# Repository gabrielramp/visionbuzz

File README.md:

# visionbuzz
A UCF Senior Design 1 project for a facial recognition vision assistant for vision-impaired users.

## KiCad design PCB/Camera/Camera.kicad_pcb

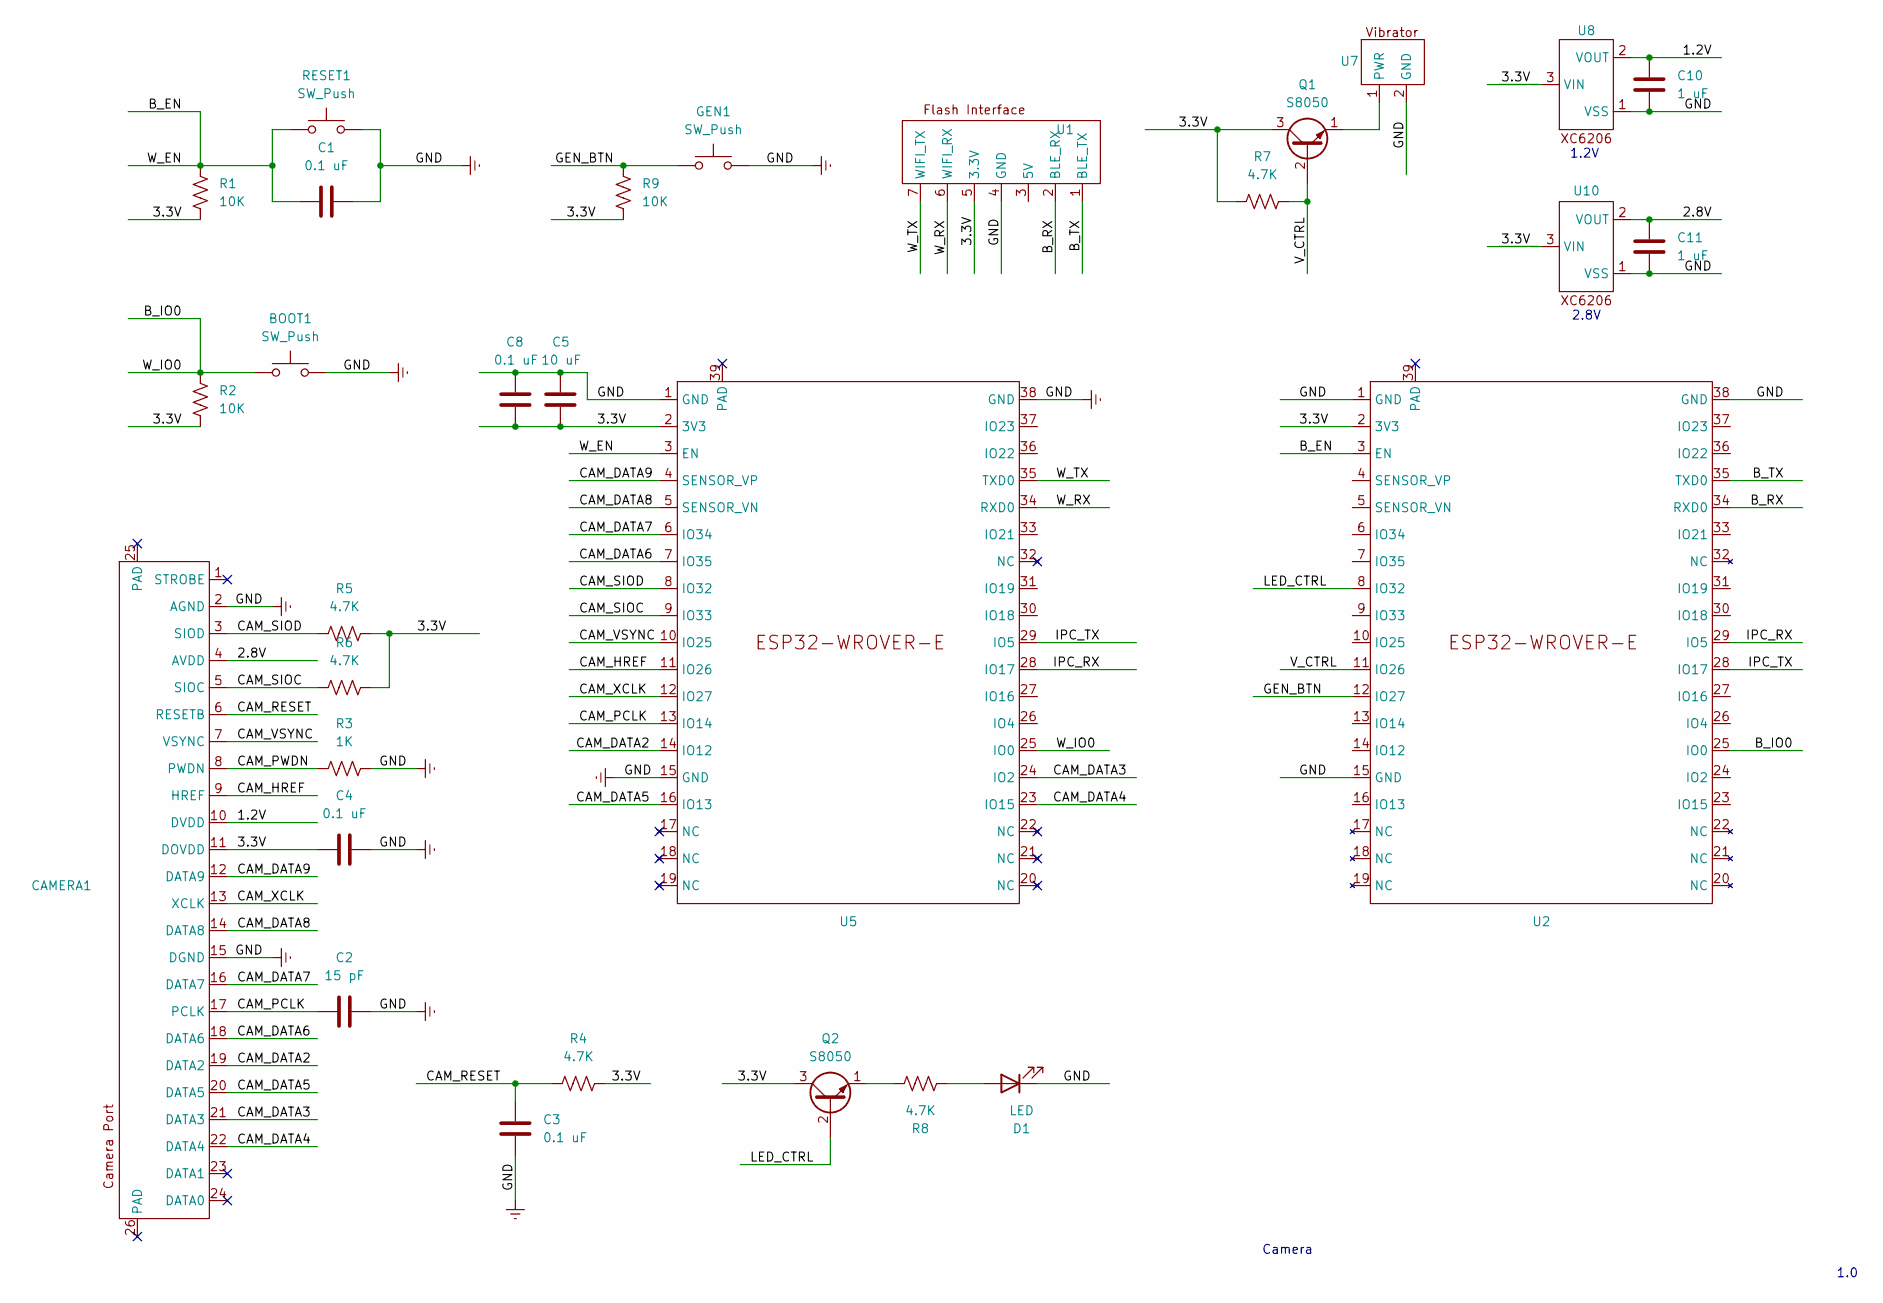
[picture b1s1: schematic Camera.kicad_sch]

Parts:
BOOT1: SW_Push; 6x6x4.3 SMD button
C1, C3, C4, C8: 0.1 uF; C_1206_3216Metric_Pad1.33x1.80mm_HandSolder
C2: 15 pF; C_1206_3216Metric_Pad1.33x1.80mm_HandSolder
C5: 10 uF; C_1206_3216Metric_Pad1.33x1.80mm_HandSolder
C10, C11: 1 uF; C_1206_3216Metric_Pad1.33x1.80mm_HandSolder
CAMERA1: 24-pin-FPC-0.5mm
D1: LED; vibration motor
GEN1: SW_Push; 6x6x4.3 SMD button
Q1, Q2: S8050; transistor
R1, R2, R9: 10K; R_1206_3216Metric_Pad1.30x1.75mm_HandSolder
R3: 1K; R_1206_3216Metric_Pad1.30x1.75mm_HandSolder
R4, R5, R6, R7, R8: 4.7K; R_1206_3216Metric_Pad1.30x1.75mm_HandSolder
RESET1: SW_Push; 6x6x4.3 SMD button
U1: Flash_Interface
U2, U5: ESP32-WROVER-E
U7: vibration motor
U8, U10: XC6206

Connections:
/1.2V: C10.2, CAMERA1.10 (DVDD), U8.2 (VOUT)
/2.8V: C11.2, CAMERA1.4 (AVDD), U10.2 (VOUT)
/3.3V: C4.1, C5.1, C8.2, CAMERA1.11 (DOVDD), Q1.3 (C), Q2.3 (C), R1.2, R2.2, R4.2, R5.1, R6.1, R7.2, R9.2, U1.5 (3.3V), U2.2 (3V3), U5.2 (3V3), U8.3 (VIN), U10.3 (VIN)
/B_EN: C1.1, R1.1, RESET1.1, U2.3 (EN), U5.3 (EN)
/B_IO0: BOOT1.1, R2.1, U2.25 (IO0), U5.25 (IO0)
/B_RX: U1.2 (BLE_RX), U2.34 (RXD0)
/B_TX: U1.1 (BLE_TX), U2.35 (TXD0)
/CAM_DATA2: CAMERA1.19 (DATA2), U5.14 (IO12)
/CAM_DATA3: CAMERA1.21 (DATA3), U5.24 (IO2)
/CAM_DATA4: CAMERA1.22 (DATA4), U5.23 (IO15)
/CAM_DATA5: CAMERA1.20 (DATA5), U5.16 (IO13)
/CAM_DATA6: CAMERA1.18 (DATA6), U5.7 (IO35)
/CAM_DATA7: CAMERA1.16 (DATA7), U5.6 (IO34)
/CAM_DATA8: CAMERA1.14 (DATA8), U5.5 (SENSOR_VN)
/CAM_DATA9: CAMERA1.12 (DATA9), U5.4 (SENSOR_VP)
/CAM_HREF: CAMERA1.9 (HREF), U5.11 (IO26)
/CAM_PCLK: C2.1, CAMERA1.17 (PCLK), U5.13 (IO14)
/CAM_PWDN: CAMERA1.8 (PWDN), R3.1
/CAM_RESET: C3.2, CAMERA1.6 (RESETB), R4.1
/CAM_SIOC: CAMERA1.5 (SIOC), R6.2, U5.9 (IO33)
/CAM_SIOD: CAMERA1.3 (SIOD), R5.2, U5.8 (IO32)
/CAM_VSYNC: CAMERA1.7 (VSYNC), U5.10 (IO25)
/CAM_XCLK: CAMERA1.13 (XCLK), U5.12 (IO27)
/GEN_BTN: GEN1.1, R9.1, U2.12 (IO27)
/IPC_RX: U2.29 (IO5), U5.28 (IO17)
/IPC_TX: U2.28 (IO17), U5.29 (IO5)
/LED_CTRL: Q2.2 (B), U2.8 (IO32)
/V_CTRL: Q1.2 (B), R7.1, U2.11 (IO26)
/W_RX: U1.6 (WIFI_RX), U5.34 (RXD0)
/W_TX: U1.7 (WIFI_TX), U5.35 (TXD0)
GNDREF: BOOT1.2, C1.2, C2.2, C3.1, C4.2, C5.2, C8.1, C10.1, C11.1, CAMERA1.2 (AGND), CAMERA1.15 (DGND), D1.1 (K), GEN1.2, R3.2, RESET1.2, U1.4 (GND), U2.1 (GND), U2.15 (GND), U2.38 (GND), U5.1 (GND), U5.15 (GND), U5.38 (GND), U7.2 (GND), U8.1 (VSS), U10.1 (VSS)
unnamed: D1.2 (A), R8.1
unnamed: Q1.1 (E), U7.1 (PWR)
unnamed: Q2.1 (E), R8.2

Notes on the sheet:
Camera
1.2V
2.8V
1.0

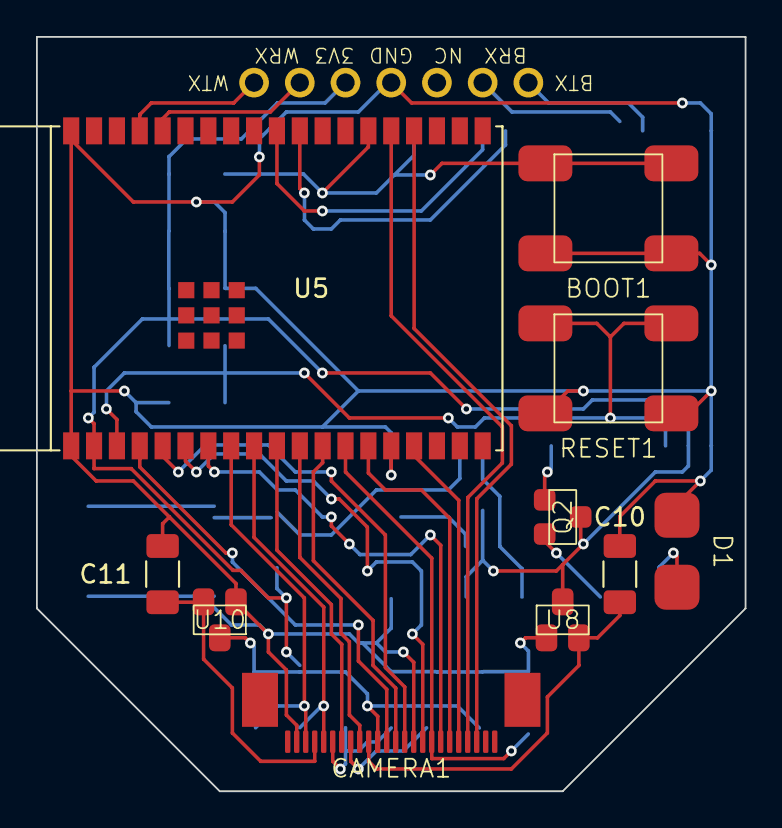
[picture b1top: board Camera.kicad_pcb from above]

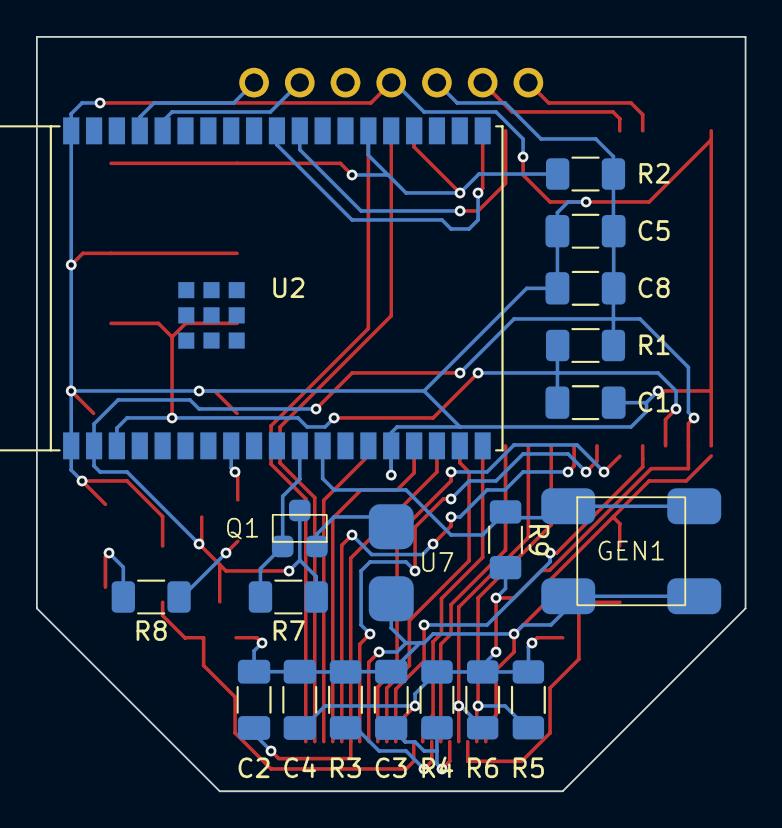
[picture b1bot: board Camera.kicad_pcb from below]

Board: 2 copper layers, 39.4 x 41.9 mm, 30 parts (19 on the bottom side), 34 nets.

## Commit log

2024-08-24 Proof of Concept Facial detection implementation
    Started code for identifying faces within the camera frame of the program. Program currently works on MacOS with Python 3.11 and in its current state is not intended for use on Raspberry Pi.
    The code can label known faces, and facial encodings are saved on disk in 'face_encodings.pkl'. Pressing 'w' will trigger learning routine if there is only one face in the frame, and a prompt to labe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
2024-08-24 Add timeline, save encodings to disk, fix crash
    Timeline records when KNOWN faces enter/exit the frame with a buffer to prevent stutters/head turns/user turns triggering enters/exits.
    Facial encodings are now saved to disk to persist between program launches.
    Fixed an issue where trying to save a facial encoding with multiple faces in the frame caused a crash.
2024-09-11 Server-Client code split
    Refactored facial detection code to split into two files, to be used separately on Client and Server devices. The Client now connects to the Server via IP and the Server should be accessible through 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
    Saving a facial embedding now functions client-side, and the client sends the frame with a designated label to the Server to be saved as a facial embedding for recognition.
    Renamed some files
2024-09-16 setup basic server framework
2024-09-16 fake login route implemented
2024-09-16 added backend gitignore
2024-09-16 changed pull_contacts to be protected route
2024-09-18 Add simple commands to setup database tables
2024-09-18 add todo for embeddings sql table
2024-09-18 basic db framework for add/delete user
2024-09-18 preliminary add contact function
2024-09-24 add test route for uploading images to server
2024-09-25 refresh token
2024-09-25 image upload
2024-09-25 add requirements
2024-10-02 secure login
2024-10-02 updated db functions
2024-10-02 Update SQL
2024-10-02 new erquirements
2024-10-02 add local API testing
2024-10-02 Update README with new info
2024-10-02 fix requirements
2024-11-04 Initialized Flutter
2024-11-04 new reqs for testing
2024-11-04 add flask tests
2024-11-04 add secure password tests
2024-11-04 add pytest config
2024-11-04 change db utils to use config name
2024-11-06 Reinitialized Flutter App
2024-11-06 byte stream
2024-11-06 Rudimentary nav bar
2024-11-11 Rudimentary navigation
2024-11-18 Basic Contacts + Better Nav
2024-11-18 good luck wormy
2024-11-21 Cleaned up contacts
2024-11-22 ai pipeline plug, test code, dotenv implementation
2024-11-22 w/Tim - Baby Bluetooth integration
2024-11-22 Rudimentary Device Pairing Page
2025-01-14 remove env .exe files
2025-01-14 new updated settings file with dotenv
2025-01-14 started moving code out of main app file
2025-01-14 rough work on making db work with config
2025-01-14 moved password stuff
2025-01-14 moved DB stuff to a class
2025-01-14 cleaned up app and changed to using services
2025-01-14 removed utils folder, redundant
2025-01-14 ignore facial data numpy folder
2025-01-14 moved face stuff out of app.py, still a bit left
2025-01-15 Basic FCM Endpoint v1
    Added an endpoint for CJ to use to attempt to connect to server
2025-01-15 Added second version of basic FCM endpoint
    Not sure which is best practice, working on implementing both for best odds at success.
2025-01-16 framework
2025-01-16 created skeleton for cluster
2025-01-16 added stuff to face_service
2025-01-16 updated settings
2025-01-16 added extension for pgvector
2025-01-16 we realized all this stuff is not needed
2025-01-16 updated README and db schema
2025-01-16 updted cluster service
2025-01-17 reworked AI services
2025-01-21 we did some things
2025-01-21 Initial commit - this build runs on the esp32c3 with dummy BLE functionality
2025-01-26 BLE integration (no deps)
2025-01-28 fleshed out local testing
2025-01-28 boop
2025-01-28 added notes on local test
2025-01-28 note for future uploads
2025-01-28 updated app to print name
2025-02-03 BLE, API, PN Work Good Enough lol
2025-02-03 imagine
2025-02-03 split project into 2 MCUs
2025-02-11 PCB changes
2025-02-12 handles firebase token ingestion
2025-02-12 more updates for firebase token
2025-02-12 instructions to run local test
2025-02-12 cloudflare integrated
2025-02-18 Added a BUTTON hell yeah
2025-02-19 Finalized PCB design
2025-02-24 new AI rec models/alignment
2025-02-24 settings update
2025-02-24 it kinda works???
2025-02-24 typo
2025-02-24 fixed up login logic
2025-03-01 Rough But Demoable
2025-03-03 fixed get contacts
2025-03-03 fixed when no clusters
2025-03-05 Not quite there but v basic
2025-03-05 added onnx
2025-03-05 jose bug fixes (i hate him)
2025-03-05 moar models
2025-03-09 Post work sesh at tim's
2025-03-09 integration stuff
2025-03-09 idk what's wrong with this it won't commit
2025-03-09 Create contactsbuggy.dart
    This version starts work on implementing clickable contacts, but is having issues with events and is not compiling. Use this as reference for the real contacts.dart
2025-03-09 Update contacts.dart
    Modified to have an API call to edit contacts.
2025-03-09 Update home.dart
    Modified to have a call to create a contact from the timeline.
2025-03-10 actually init firebase
2025-03-10 db fixes for instant notif
2025-03-10 edit testing
2025-03-10 arcface
2025-03-10 testing
2025-03-10 edit should work now
2025-03-10 BLE changes
2025-03-10 shorter notif
2025-03-11 pray
2025-03-11 please loard
2025-03-11 loard
2025-03-11 everything is gucci :D
2025-03-11 Monday integration sesh
2025-03-11 delete?
2025-03-11 Pre-elevator code
2025-03-11 Boosted timeline
2025-03-11 Improved contacts
2025-03-12 Pre-full integration
2025-03-12 Good vibes
2025-03-12 Pre blaze
2025-03-12 please
2025-03-12 [lease
2025-03-12 doot
2025-03-12 Good stopping point, token works
2025-03-12 demo build
2025-03-12 print for real notif
2025-03-12 sajbkjj
2025-03-12 don't save imagees anymore
2025-03-16 Post-demo (don't do full write)
2025-03-16 Couple QoL things
2025-03-26 Update settings.py
    better threshold
2025-03-27 save
2025-03-30 qweqweqwe
2025-03-30 reversed vibration order
2025-03-31 TTS For notifs, Bigger Text, Better Device Page, Rough about page
2025-03-31 Test Background Notif
2025-03-31 Revert "Test Background Notif"
    This reverts commit 5607a4eacd7be6d5580ff5df033218ca2fd21646.
2025-03-31 Undoing previous APNS Change
    Fix Server Issue
2025-03-31 No more touching
